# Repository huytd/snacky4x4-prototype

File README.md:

Snacky 4x4 keyboard PCB

https://thefullsnack.com/tags/keyboard-building.html

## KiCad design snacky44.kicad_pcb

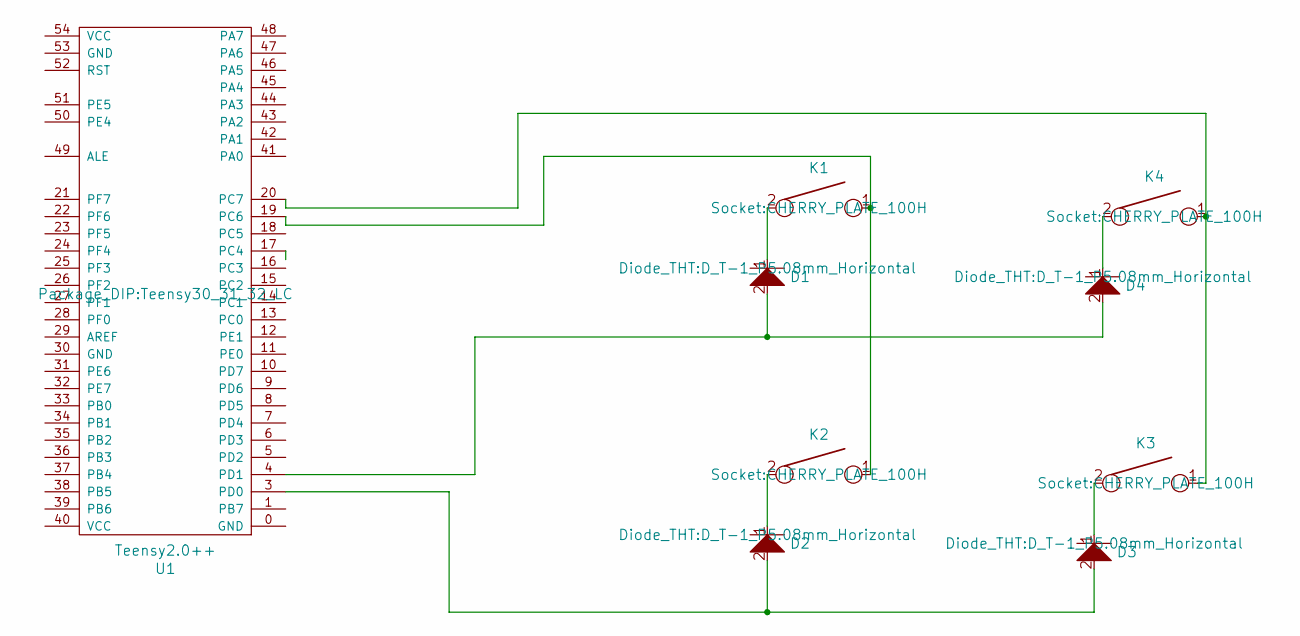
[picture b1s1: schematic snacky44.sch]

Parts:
D1, D2, D3, D4: D; D_T-1_P5.08mm_Horizontal
K1, K2, K3, K4: KEYSW; CHERRY_PLATE_100H
U1: Teensy2.0++; Teensy30_31_32_LC

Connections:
unnamed: D1.1, K1.2
unnamed: D1.2, D4.2, U1.4 (PD1)
unnamed: D2.1, K2.2
unnamed: D2.2, D3.2, U1.3 (PD0)
unnamed: D3.1, K3.2
unnamed: D4.1, K4.2
unnamed: K1.1, K2.1, U1.19 (PC6)
unnamed: K3.1, K4.1, U1.20 (PC7)

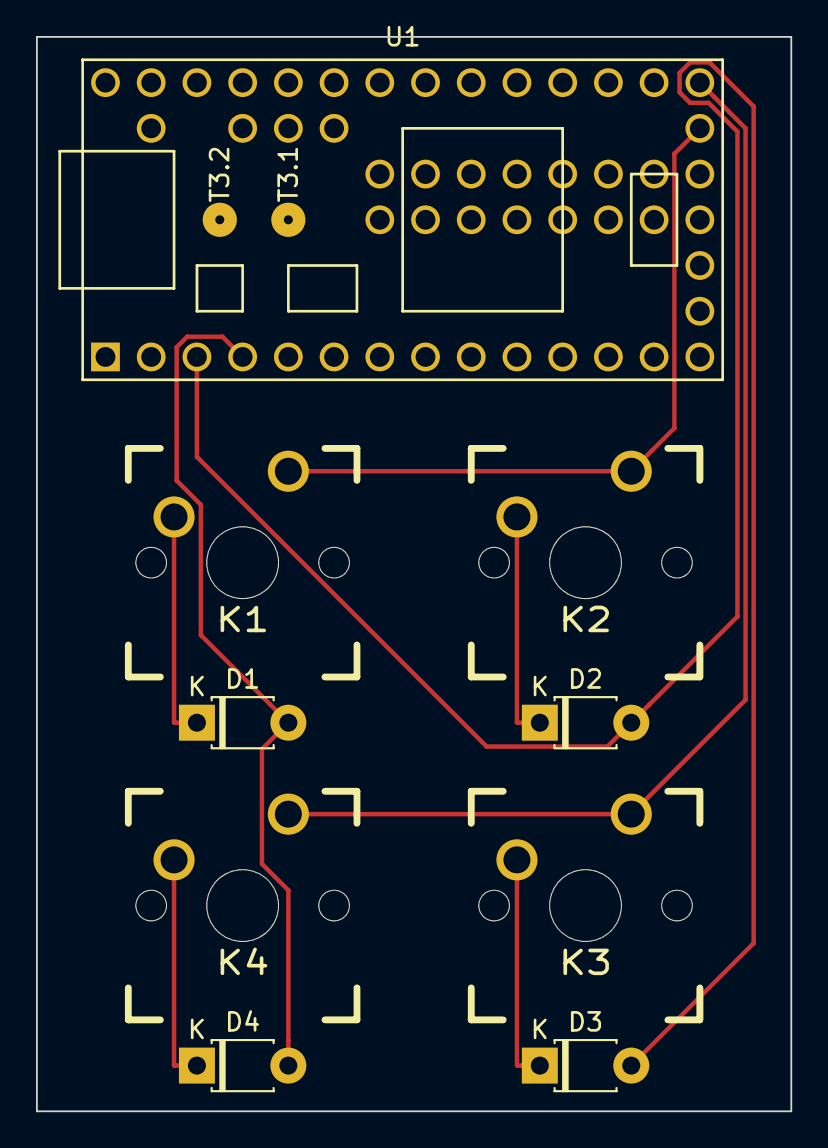
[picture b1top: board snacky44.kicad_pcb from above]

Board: 2 copper layers, 41.9 x 59.7 mm, 9 parts (0 on the bottom side), 8 nets.

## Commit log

2018-12-20 initial
